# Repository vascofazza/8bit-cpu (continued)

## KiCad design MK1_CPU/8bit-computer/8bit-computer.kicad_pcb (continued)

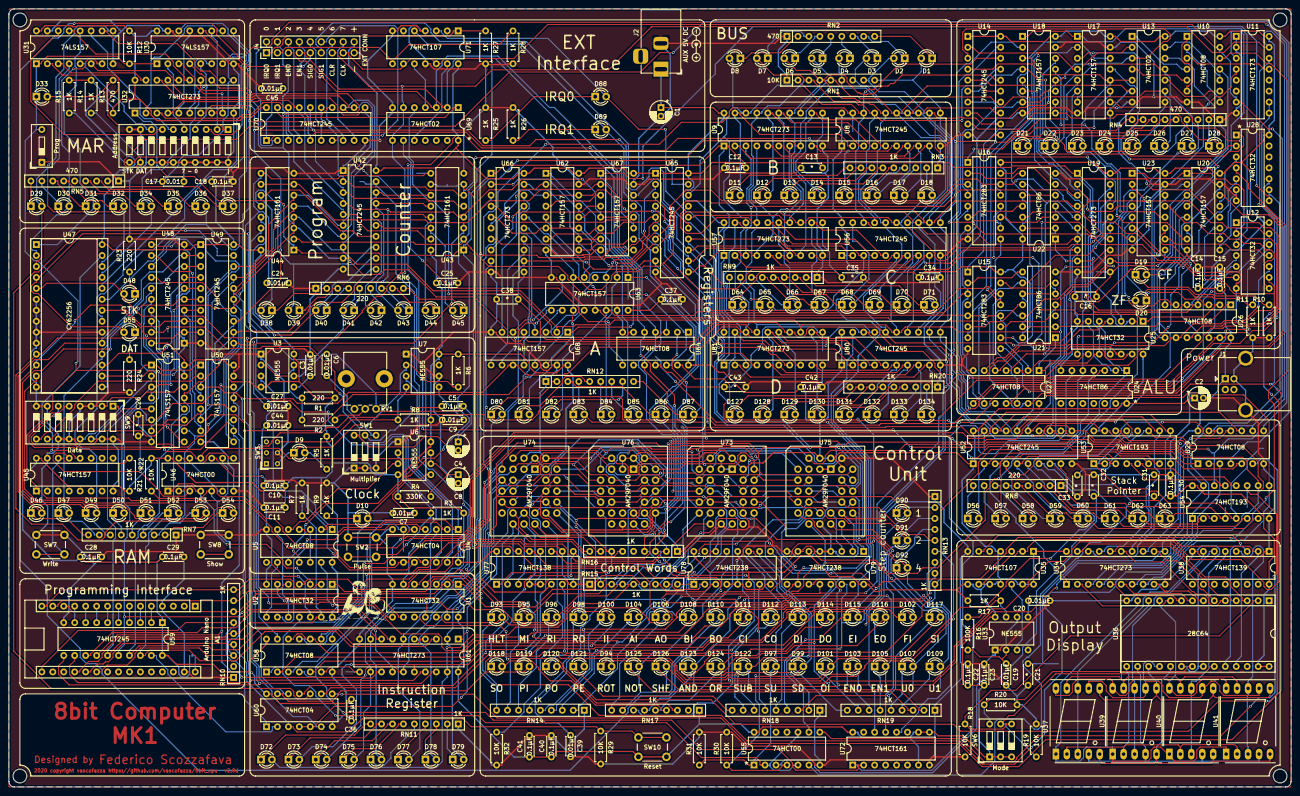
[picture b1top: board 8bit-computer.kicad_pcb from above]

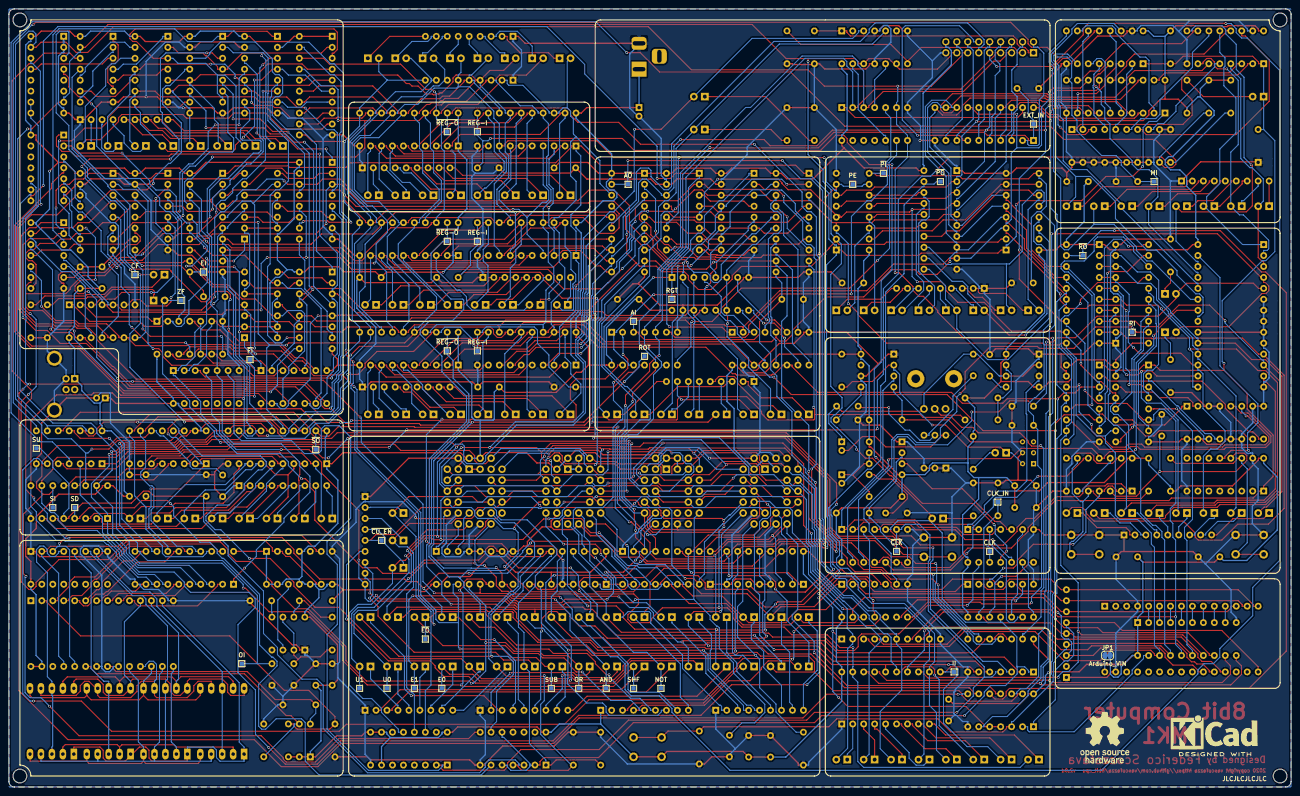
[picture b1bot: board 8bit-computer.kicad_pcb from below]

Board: 2 copper layers, 297.2 x 180.3 mm, 377 parts (44 on the bottom side), 516 nets.

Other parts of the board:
G0: LOGO; parrot
G1: Symbol_Barrel_Polarity
G2: KiCad-Logo2_8mm_SilkScreen
G3: OSHW-Logo_11.4x12mm_SilkScreen
MH0, MH1, MH2, MH3: MountingHole_3.2mm_M3
TP4, TP40: ~{REG-O}; TestPoint_Pad_1.0x1.0mm

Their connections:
/Control logic/~BO: TP4.1; also elsewhere on the board
/Control logic/~DO: TP40.1; also elsewhere on the board

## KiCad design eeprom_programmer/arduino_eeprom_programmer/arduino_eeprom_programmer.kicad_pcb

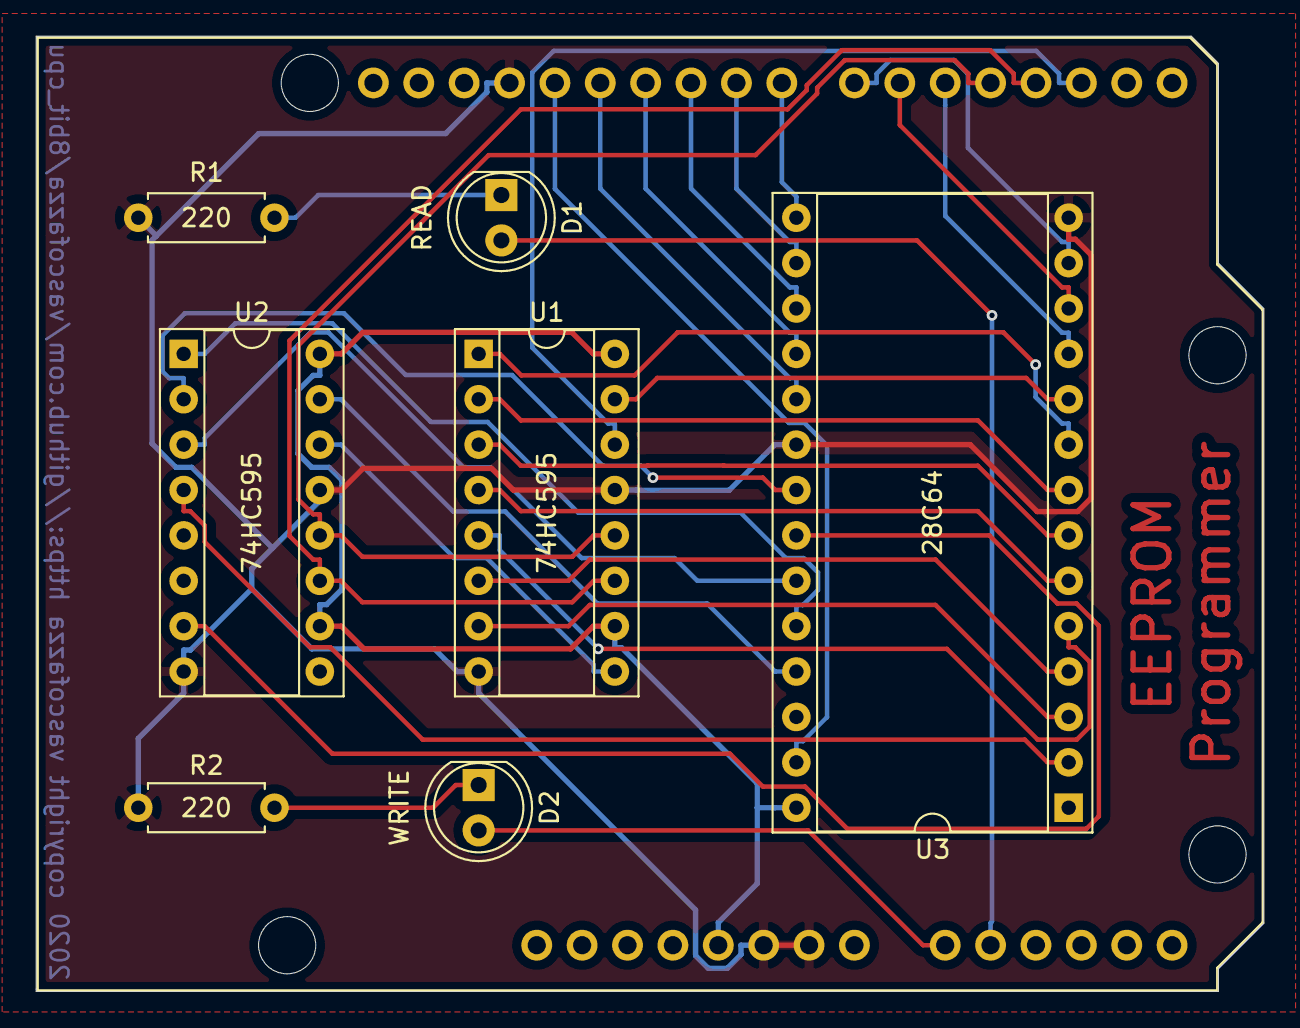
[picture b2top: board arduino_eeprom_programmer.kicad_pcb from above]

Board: 2 copper layers, 68.7 x 53.5 mm, 8 parts (0 on the bottom side), 33 nets.

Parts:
D1: READ; LED_D5.0mm
D2: WRITE; LED_D5.0mm
R1, R2: 220; R_Axial_DIN0207_L6.3mm_D2.5mm_P7.62mm_Horizontal
U1, U2: 74HC595; DIP-16_W7.62mm_Socket
U3: 28C64; DIP-28_W15.24mm_Socket
XA1: Arduino_Uno_Shield

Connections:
GND: R1.1, R2.1, U1.8, U1.13, U2.8, U2.13, U3.14, U3.20, XA1.GND1, XA1.GND2, XA1.GND3
unnamed: D1.1, R1.2
unnamed: D1.2, XA1.A1
unnamed: D2.1, R2.2
unnamed: D2.2, XA1.A0
unnamed: U1.1, U3.9
unnamed: U1.2, U3.8
unnamed: U1.3, U3.7
unnamed: U1.4, U3.6
unnamed: U1.5, U3.5
unnamed: U1.6, U3.4
unnamed: U1.7, U3.3
unnamed: U1.9, U2.14
unnamed: U1.11, U2.11, XA1.D3
unnamed: U1.12, U2.12, XA1.D4
unnamed: U1.14, XA1.D2
unnamed: U1.15, U3.10
unnamed: U2.1, U3.24
unnamed: U2.2, U3.21
unnamed: U2.3, U3.23
unnamed: U2.4, U3.2
unnamed: U2.7, U3.22
unnamed: U2.15, U3.25
unnamed: U3.11, XA1.D5
unnamed: U3.12, XA1.D6
unnamed: U3.13, XA1.D7
unnamed: U3.15, XA1.D8
unnamed: U3.16, XA1.D9
unnamed: U3.17, XA1.D10
unnamed: U3.18, XA1.D11
unnamed: U3.19, XA1.D12
unnamed: U3.27, XA1.D13
VCC: U1.10, U1.16, U2.10, U2.16, U3.28, XA1.5V1

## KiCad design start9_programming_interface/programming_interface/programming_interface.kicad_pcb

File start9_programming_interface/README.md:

# Start9 Programming Interface

An ATmega328-driven programming interface for the MK1 8-bit CPU.

## Description

Writes a program, stored in a flash memory, into the working memory of the MK1 CPU.

Supports up to 16 program slots, the program/next button is used to select the bank and write the selected program.

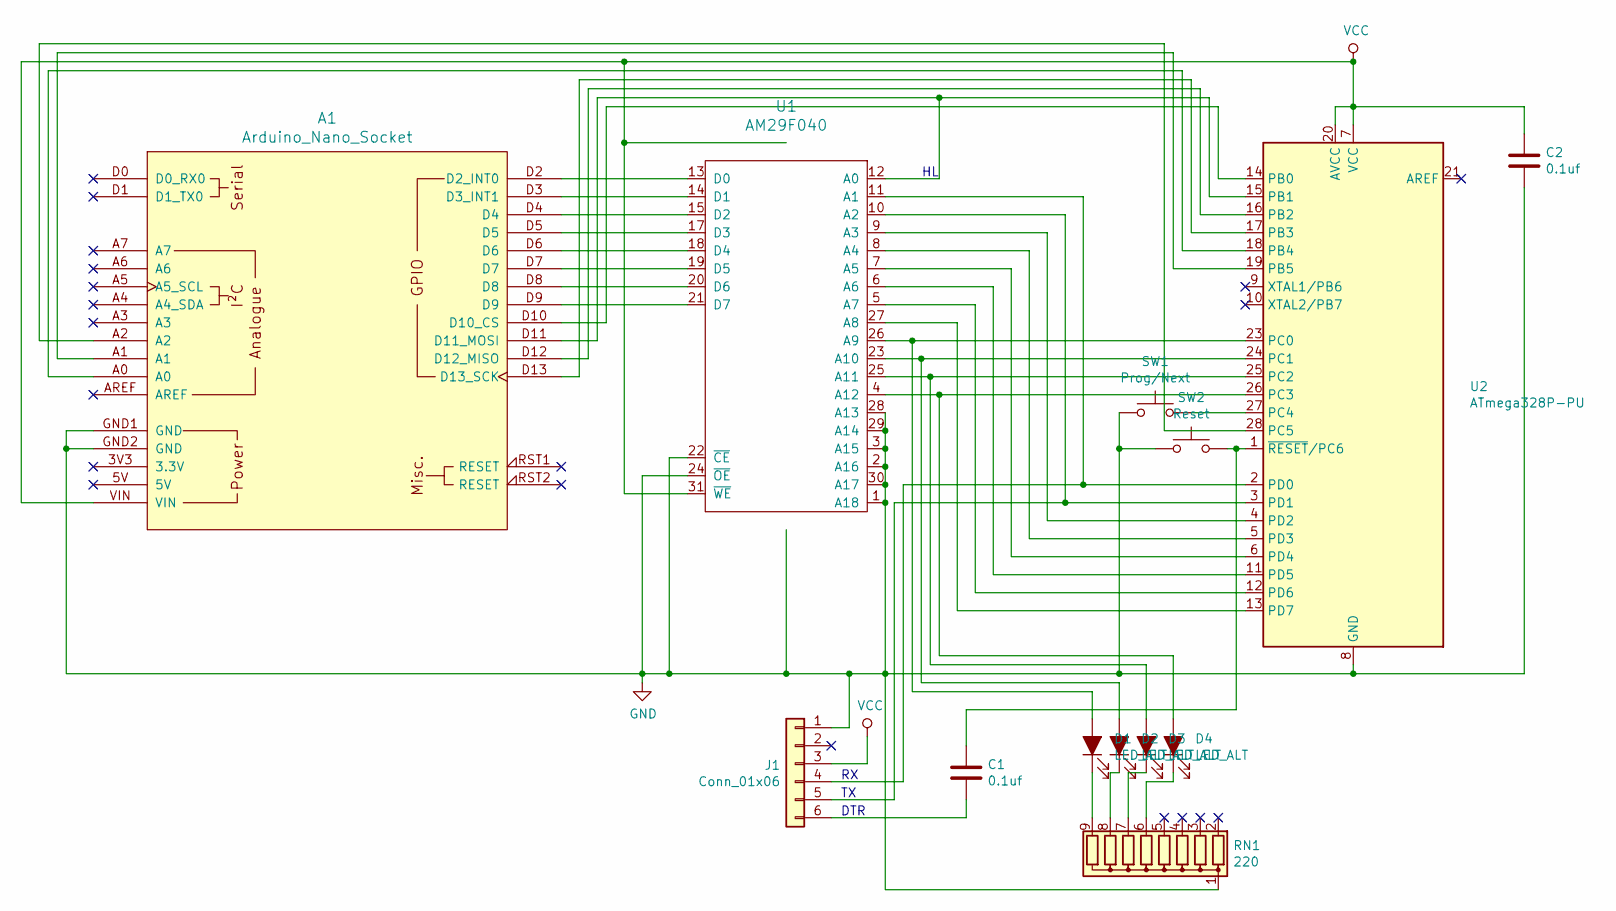
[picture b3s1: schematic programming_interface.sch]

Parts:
A1: Arduino_Nano_Socket
C1, C2: 0.1uf; C_Disc_D4.3mm_W1.9mm_P5.00mm
D1, D2, D3, D4: LED_ALT; LED_D3.0mm
J1: Conn_01x06; PinSocket_1x06_P2.54mm_Vertical
RN1: 220; R_Array_SIP9
SW1: Prog/Next; SW_PUSH_6mm_H5mm
SW2: Reset; SW_PUSH_6mm_H5mm
U1: AM29F040; PLCC-32_THT-Socket
U2: ATmega328P-PU; DIP-28_W7.62mm_Socket

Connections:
GND: A1.GND1 (GND), A1.GND2 (GND), C2.2, J1.1, RN1.1 (common), SW1.1, SW2.1, U1.1 (A18), U1.2 (A16), U1.3 (A15), U1.16 (GND), U1.22 (~CE~), U1.24 (~OE~), U1.28 (A13), U1.29 (A14), U1.30 (A17), U2.8 (GND), U2.22 (GND)
unnamed: A1.A0, U2.18 (PB4)
unnamed: A1.A1, U2.19 (PB5)
unnamed: A1.A2, U2.28 (PC5)
unnamed: A1.D2 (D2_INT0), U1.13 (D0)
unnamed: A1.D3 (D3_INT1), U1.14 (D1)
unnamed: A1.D4, U1.15 (D2)
unnamed: A1.D5, U1.17 (D3)
unnamed: A1.D6, U1.18 (D4)
unnamed: A1.D7, U1.19 (D5)
unnamed: A1.D8, U1.20 (D6)
unnamed: A1.D9, U1.21 (D7)
unnamed: A1.D10 (D10_CS), U2.14 (PB0)
unnamed: A1.D11 (D11_MOSI), U1.12 (A0), U2.15 (PB1)
unnamed: A1.D12 (D12_MISO), U2.16 (PB2)
unnamed: A1.D13 (D13_SCK), U2.17 (PB3)
unnamed: C1.1, SW2.2, U2.1 (~RESET~/PC6)
unnamed: C1.2, J1.6
unnamed: D1.1 (K), RN1.9 (R8)
unnamed: D1.2 (A), U1.26 (A9), U2.23 (PC0)
unnamed: D2.1 (K), RN1.8 (R7)
unnamed: D2.2 (A), U1.23 (A10), U2.24 (PC1)
unnamed: D3.1 (K), RN1.7 (R6)
unnamed: D3.2 (A), U1.25 (A11), U2.25 (PC2)
unnamed: D4.1 (K), RN1.6 (R5)
unnamed: D4.2 (A), U1.4 (A12), U2.26 (PC3)
unnamed: J1.4, U1.11 (A1), U2.2 (PD0)
unnamed: J1.5, U1.10 (A2), U2.3 (PD1)
unnamed: SW1.2, U2.27 (PC4)
unnamed: U1.5 (A7), U2.12 (PD6)
unnamed: U1.6 (A6), U2.11 (PD5)
unnamed: U1.7 (A5), U2.6 (PD4)
unnamed: U1.8 (A4), U2.5 (PD3)
unnamed: U1.9 (A3), U2.4 (PD2)
unnamed: U1.27 (A8), U2.13 (PD7)
VCC: A1.VIN, C2.1, J1.3, U1.31 (~WE~), U1.32 (VCC), U2.7 (VCC), U2.20 (AVCC)

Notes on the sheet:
DTR

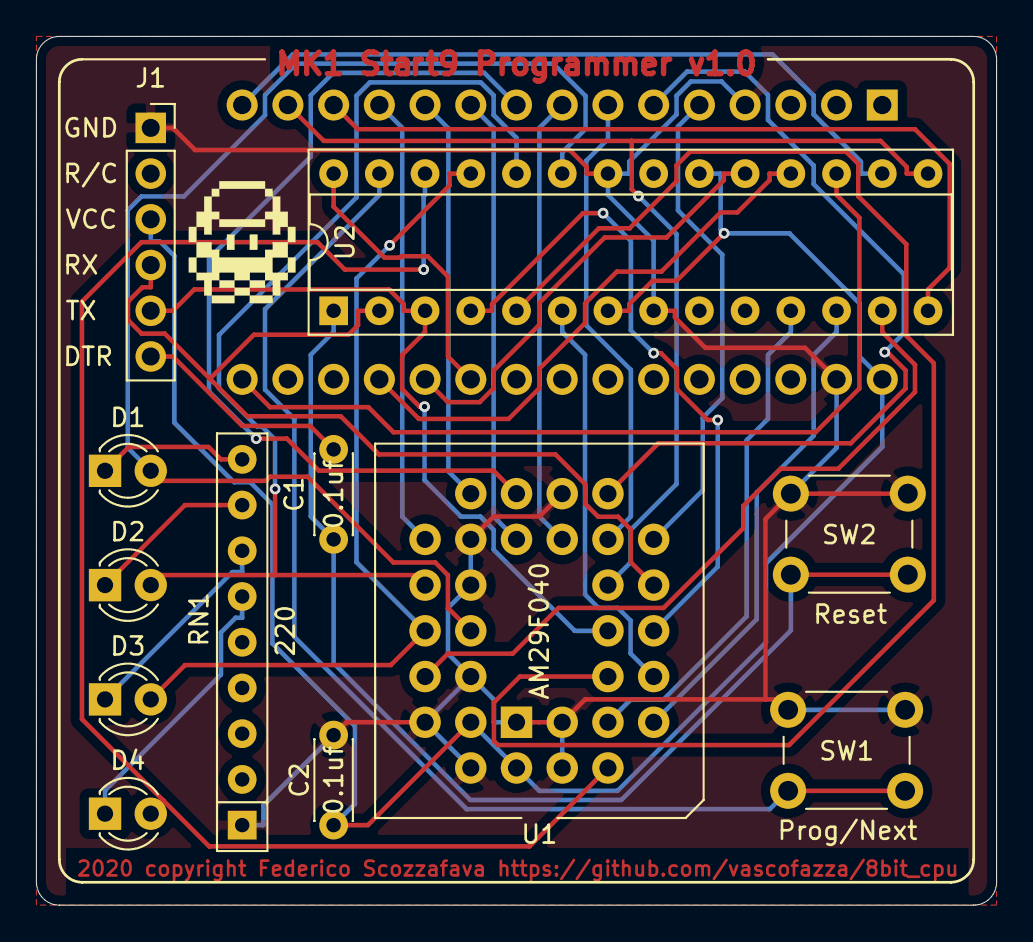
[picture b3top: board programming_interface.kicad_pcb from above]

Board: 2 copper layers, 53.3 x 48.3 mm, 15 parts (1 on the bottom side), 36 nets.

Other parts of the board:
S0: LOGO; trainer_tiny
S1: LOGO; parrot_small

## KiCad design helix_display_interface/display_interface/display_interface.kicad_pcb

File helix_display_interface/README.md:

# Helix Display Interface

An ATmega328-driven LCD Display peripheral for the MK1 8-bit CPU.

## Description

LCD character display interface for the MK1 CPU computer.

Uses an ATmega328P as driver and implements Integer and Character output mode.

Commands and data are both transmitted on the external bus.

There are two external bus connectors for peripheral daisy chaining.

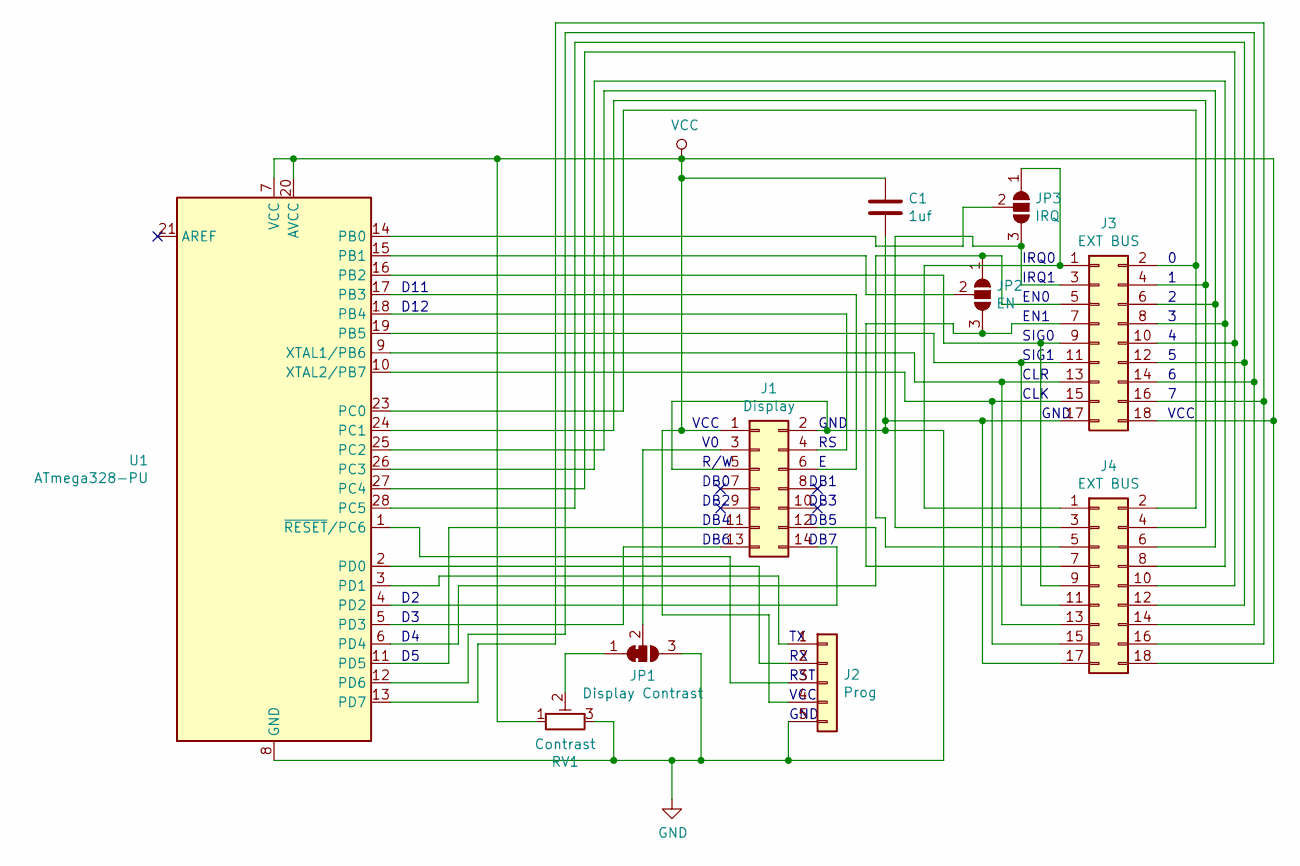
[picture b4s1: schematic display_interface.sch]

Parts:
C1: 1uf; C_Disc_D4.3mm_W1.9mm_P5.00mm
J1: Display; PinSocket_2x07_P2.54mm_Vertical
J2: Prog; PinSocket_1x05_P2.54mm_Vertical
J3, J4: EXT BUS; PinHeader_2x09_P2.54mm_Vertical
JP1: Display Contrast; SolderJumper-3_P1.3mm_Bridged12_RoundedPad1.0x1.5mm_NumberL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
JP2: EN; SolderJumper-3_P1.3mm_Open_RoundedPad1.0x1.5mm_NumberLabels
JP3: IRQ; SolderJumper-3_P1.3mm_Open_RoundedPad1.0x1.5mm_NumberLabels
RV1: Contrast; Potentiometer_Piher_PT-10-V10_Vertical
U1: ATmega328-PU; DIP-28_W7.62mm_Socket

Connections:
GND: C1.2, J1.2, J1.5, J2.5, J3.17, J4.17, JP1.3 (B), RV1.3, U1.8 (GND), U1.22 (GND)
unnamed: J1.3, JP1.2 (C)
unnamed: J1.4, U1.18 (PB4)
unnamed: J1.6, U1.17 (PB3)
unnamed: J1.11, U1.11 (PD5)
unnamed: J1.12, U1.6 (PD4)
unnamed: J1.13, U1.5 (PD3)
unnamed: J1.14, U1.4 (PD2)
unnamed: J2.1, U1.3 (PD1)
unnamed: J2.2, U1.2 (PD0)
unnamed: J2.3, U1.1 (~RESET~/PC6)
unnamed: J3.1, J4.1, JP3.1 (A)
unnamed: J3.2, J4.2, U1.23 (PC0)
unnamed: J3.3, J4.3, JP3.3 (B)
unnamed: J3.4, J4.4, U1.24 (PC1)
unnamed: J3.5, J4.5, JP2.1 (A)
unnamed: J3.6, J4.6, U1.25 (PC2)
unnamed: J3.7, J4.7, JP2.3 (B)
unnamed: J3.8, J4.8, U1.26 (PC3)
unnamed: J3.9, J4.9, U1.16 (PB2)
unnamed: J3.10, J4.10, U1.27 (PC4)
unnamed: J3.11, J4.11, U1.19 (PB5)
unnamed: J3.12, J4.12, U1.28 (PC5)
unnamed: J3.13, J4.13, U1.9 (XTAL1/PB6)
unnamed: J3.14, J4.14, U1.12 (PD6)
unnamed: J3.15, J4.15, U1.10 (XTAL2/PB7)
unnamed: J3.16, J4.16, U1.13 (PD7)
unnamed: JP1.1 (A), RV1.2
unnamed: JP2.2 (C), U1.15 (PB1)
unnamed: JP3.2 (C), U1.14 (PB0)
VCC: C1.1, J1.1, J2.4, J3.18, J4.18, RV1.1, U1.7 (VCC), U1.20 (AVCC)

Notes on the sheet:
VCC
GND
R/W
DB0
DB1
DB2
DB3
DB4
DB5
DB6
DB7
D12
D11
RST
IRQ0
IRQ1
EN0
EN1
SIG0
SIG1
CLR
CLK

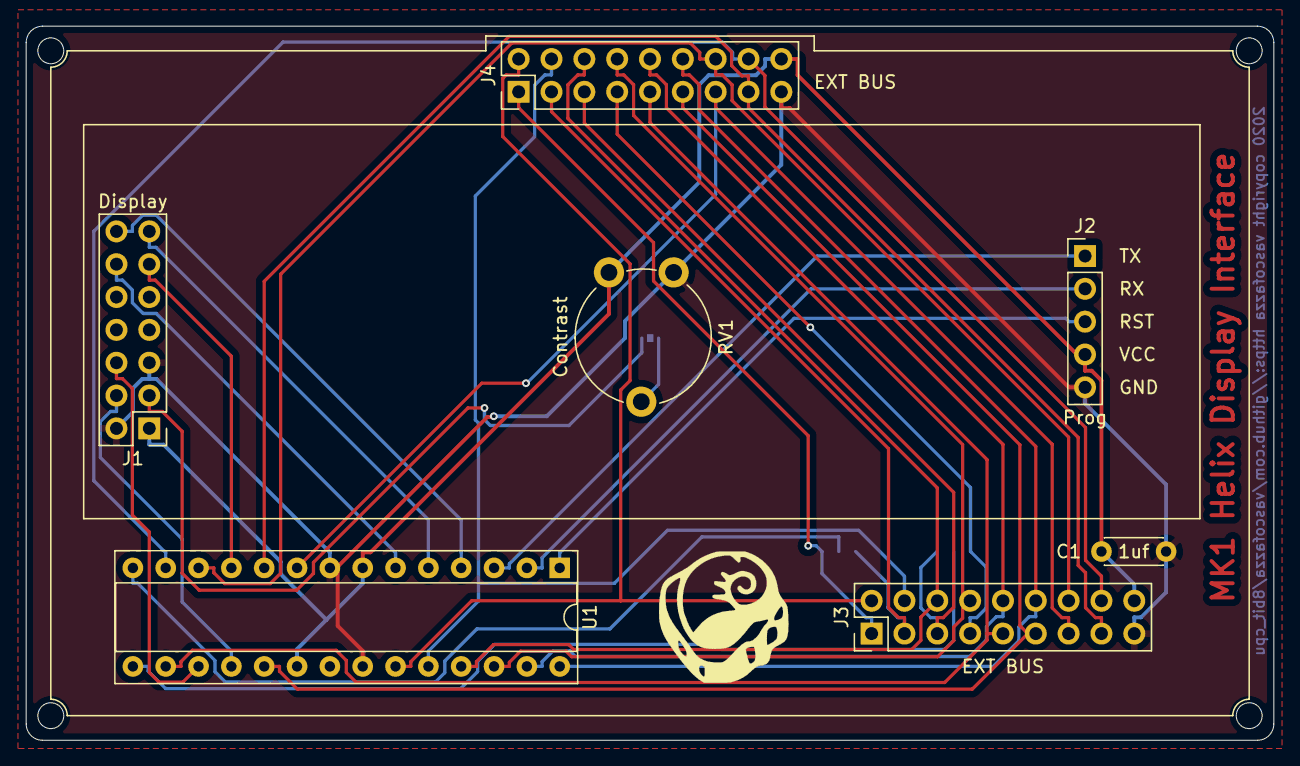
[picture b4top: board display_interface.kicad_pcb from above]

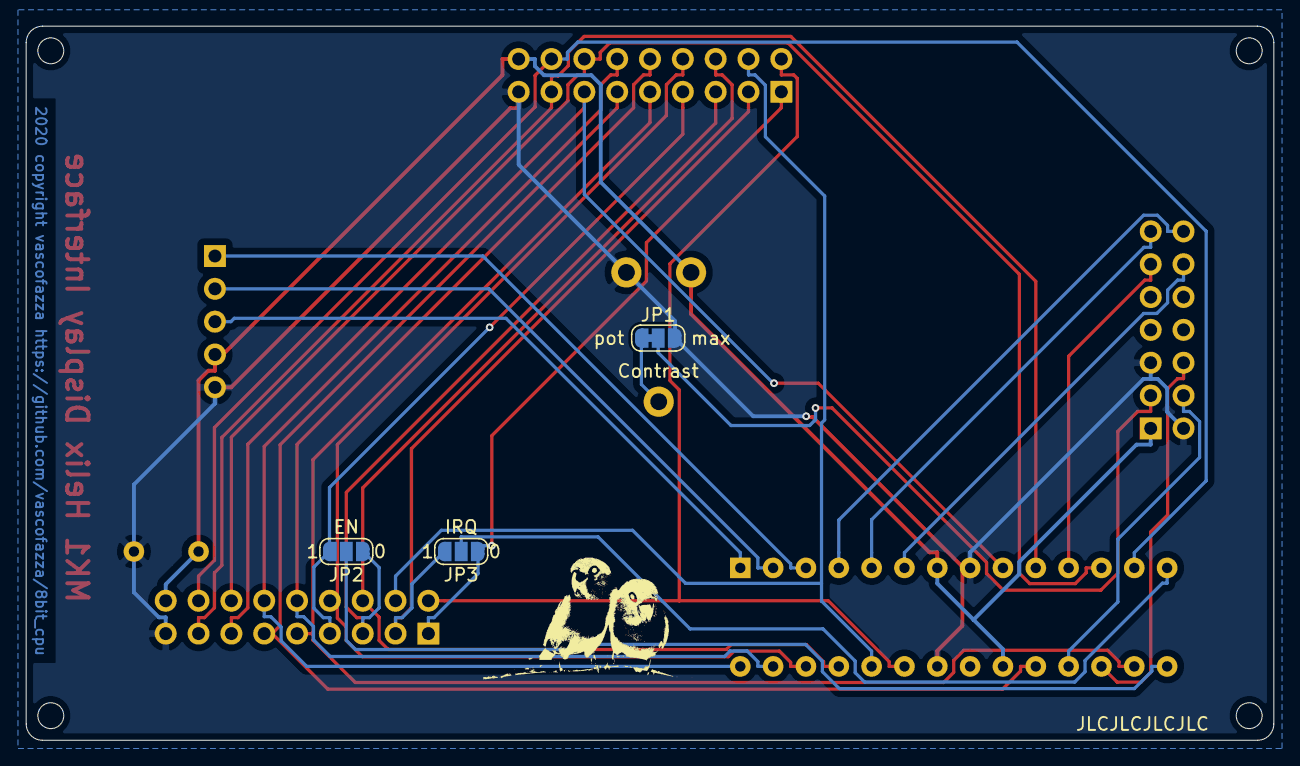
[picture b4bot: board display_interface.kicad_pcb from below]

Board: 2 copper layers, 96.5 x 55.2 mm, 16 parts (4 on the bottom side), 31 nets.

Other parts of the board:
M0, M1, M2, M3: MountingHole_2mm
S0: LOGO; parrot
S1: LOGO; helix_small

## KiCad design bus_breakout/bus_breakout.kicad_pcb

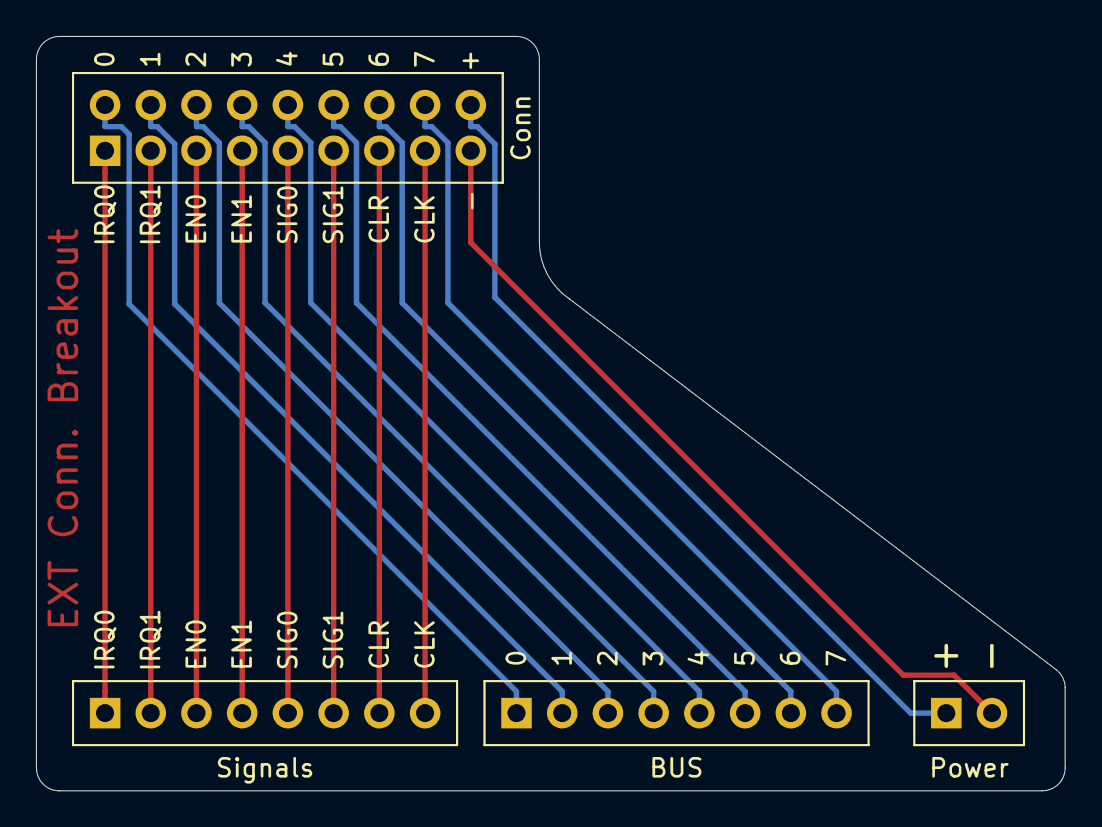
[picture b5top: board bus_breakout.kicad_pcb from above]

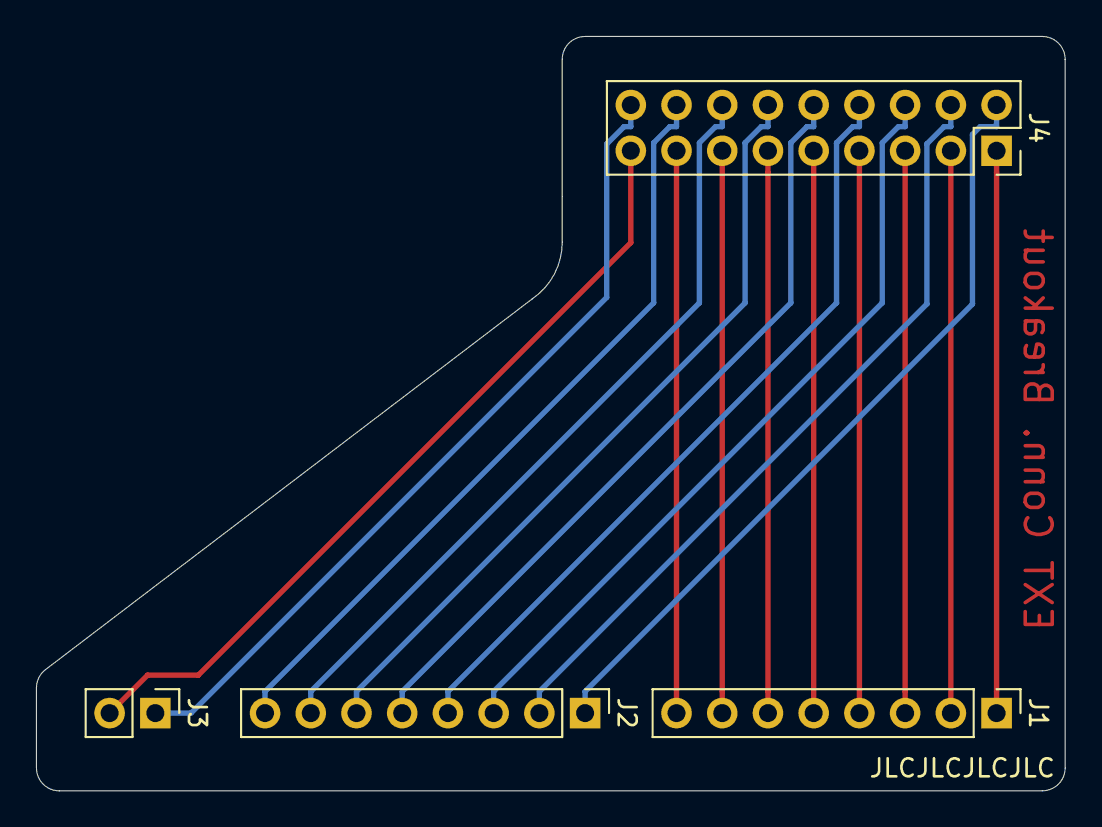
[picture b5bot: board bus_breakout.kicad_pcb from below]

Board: 2 copper layers, 57.1 x 41.9 mm, 4 parts (3 on the bottom side), 18 nets.

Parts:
J1: Signals; PinHeader_1x08_P2.54mm_Vertical
J2: BUS; PinHeader_1x08_P2.54mm_Vertical
J3: Power; PinHeader_1x02_P2.54mm_Vertical
J4: Conn; PinHeader_2x09_P2.54mm_Vertical

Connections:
unnamed: J1.1, J4.1
unnamed: J1.2, J4.3
unnamed: J1.3, J4.5
unnamed: J1.4, J4.7
unnamed: J1.5, J4.9
unnamed: J1.6, J4.11
unnamed: J1.7, J4.13
unnamed: J1.8, J4.15
unnamed: J2.1, J4.2
unnamed: J2.2, J4.4
unnamed: J2.3, J4.6
unnamed: J2.4, J4.8
unnamed: J2.5, J4.10
unnamed: J2.6, J4.12
unnamed: J2.7, J4.14
unnamed: J2.8, J4.16
unnamed: J3.1, J4.18
unnamed: J3.2, J4.17
